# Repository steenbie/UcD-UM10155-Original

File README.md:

# UcD-UM10155-Original

-[ ] Bring schematic back to original
-[ ] Complete layout

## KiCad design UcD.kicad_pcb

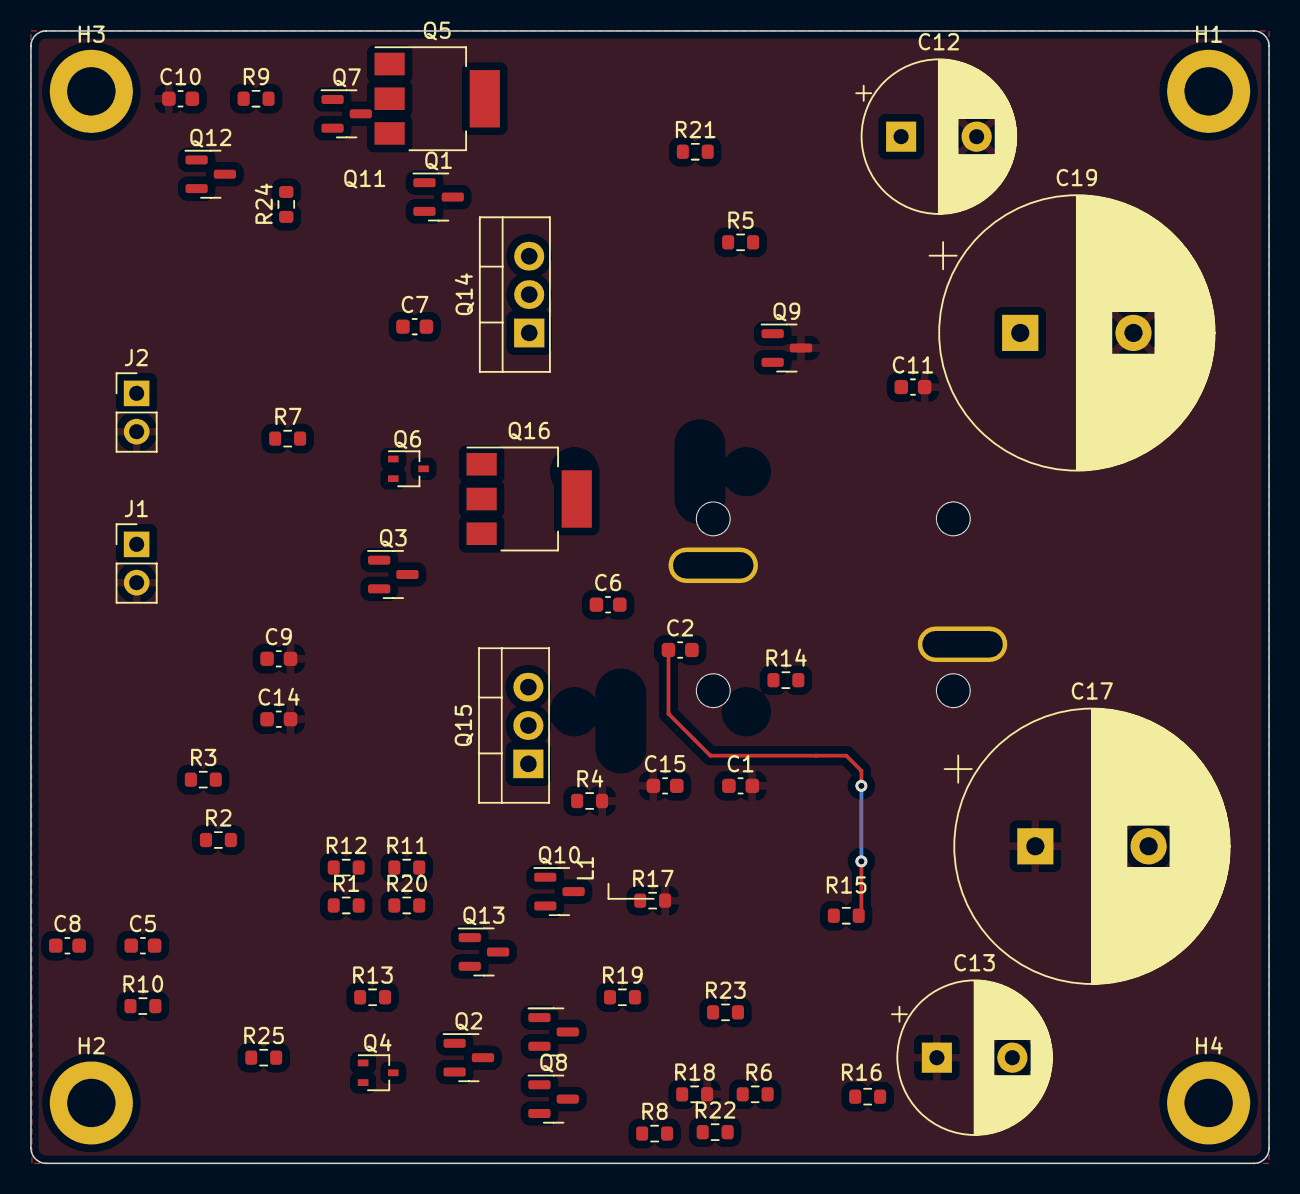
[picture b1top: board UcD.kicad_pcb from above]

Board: 2 copper layers, 82.0 x 75.0 mm, 63 parts (0 on the bottom side), 35 nets.

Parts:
C1: 4n7; C_0603_1608Metric
C2: 220p; C_0603_1608Metric
C5, C6, C9, C10, C14, C15: 100n; C_0603_1608Metric
C7, C8: 100p; C_0603_1608Metric
C11: 680n; C_0603_1608Metric
C12, C13: 22u; CP_Radial_D10.0mm_P5.00mm
C17, C19: 470u; CP_Radial_D18.0mm_P7.50mm
H1, H2, H3, H4: MountingHole; MountingHole_3.2mm_M3_ISO14580_Pad
J1, J2: Conn_01x02_Male; PinHeader_1x02_P2.54mm_Vertical
L1: AGP2923-103KL; Inductor_Coilcraft_AGP2923-103KL-17.0x27.0mm
Q1, Q8: BF821; SOT-23
Q2, Q7, Q9: BC847; SOT-23
Q3, Q10, Q11, Q12, Q13: BC857; SOT-23
Q4, Q6: BF820; SOT-323_SC-70
Q5: BF721; SOT-223
Q14, Q15: IRF540N; TO-220-3_Vertical
Q16: PZT2222A; SOT-223
R1: 560R; R_0603_1608Metric
R2: R47k_0603; R_0603_1608Metric
R3: 47k; R_0603_1608Metric
R4: 1k; R_0603_1608Metric
R5, R11: R220R_0603; R_0603_1608Metric
R6, R10: R47R_0603; R_0603_1608Metric
R7: 220R; R_0603_1608Metric
R8: R330R_0603; R_0603_1608Metric
R9, R12: 10R; R_0603_1608Metric
R13: R5M6_0603; R_0603_1608Metric
R14: R3M9_0603; R_0603_1608Metric
R15: R2k2_0603; R_0603_1608Metric
R16: R22k_0603; R_0603_1608Metric
R17, R24, R25: R1k0_0603; R_0603_1608Metric
R18: R8k2_0603; R_0603_1608Metric
R19: R4k7_0603; R_0603_1608Metric
R20, R21: R390R_0603; R_0603_1608Metric
R22, R23: R27R_0603; R_0603_1608Metric

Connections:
GND: C1.2, C9.2, C10.1, C11.2, C12.2, C13.1, C14.2, C15.1, C17.1, C19.2, J1.2, J2.2, Q9.3 (C), R4.2, R17.2, R18.2
unnamed: C1.1, Q1.1 (B), R1.1, R4.1
unnamed: C2.1, R15.2
unnamed: C2.2, Q8.1 (B), R13.2, R14.1, R16.2, R17.1
unnamed: C5.1, Q10.2 (E), R19.2, R20.1
unnamed: C5.2, C7.2, L1.1, Q12.3 (C), Q14.3 (S), Q15.2 (D), R24.2
unnamed: C6.1, Q11.2 (E), R21.1
unnamed: C6.2, C8.2, C10.2, C13.2, Q13.3 (C), Q15.3 (S), R25.2
unnamed: C11.1, L1.2, R15.1, R16.1
unnamed: C9.1, C12.1, Q14.2 (D)
unnamed: C14.1, C19.1, R9.1, R13.1, R19.1
unnamed: C15.2, C17.2, R12.1, R14.2
unnamed: Q1.3 (C), Q2.3 (C), Q4.1 (B)
unnamed: Q6.1 (B), Q7.3 (C), Q8.3 (C)
unnamed: Q9.1 (B), R18.1
unnamed: Q4.3 (C), Q10.1 (B), R20.2
unnamed: Q10.3 (C), R22.2
unnamed: Q6.3 (C), Q11.1 (B), R21.2
unnamed: Q11.3 (C), R23.2
unnamed: Q12.2 (E), Q14.1 (G)
unnamed: Q12.1 (B), R22.1, R24.1
unnamed: Q13.2 (E), Q15.1 (G)
unnamed: Q13.1 (B), R23.1, R25.1
unnamed: J1.1, R2.2
unnamed: J2.1, R1.2
unnamed: Q1.2 (E), R6.2
unnamed: Q2.1 (B), Q4.2 (E), Q6.2 (E), Q7.1 (B), R8.1
unnamed: Q2.2 (E), R5.1
unnamed: Q3.1 (B), Q5.2 (E), R7.2
unnamed: Q3.2 (E), R3.1, R7.1, R9.2
unnamed: Q3.3 (C), Q5.1 (B), R2.1, R3.2
unnamed: Q5.3 (C), R6.1, R10.2
unnamed: Q7.2 (E), R11.1
unnamed: Q8.2 (E), R10.1
unnamed: R5.2, R8.2, R11.2, R12.2

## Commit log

2022-02-22 AGP2923 STEP model added
2022-03-24 schematic updates
